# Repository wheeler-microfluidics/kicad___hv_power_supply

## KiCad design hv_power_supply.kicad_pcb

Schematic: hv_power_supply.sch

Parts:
C1: 100uF, 35V; TantalC_SizeE_EIA-7360_Reflow
C2, C3: 100nF; C_0805
C4: 4u7,250V; c_elec_8x10.5
C5: 10uF; TantalC_SizeD_EIA-7343_Reflow
C6: 100nF,250V; C_1812
D1: ES2F; DO-214BA
L1: 100uH; self_cms_we-pd3
P1: CONN_01X09; Pin_Header_Straight_1x09
Q1: IRF644PBF; TO-220_Neutral123_Vertical
R1: 10k; R_0805
R2: 1M5; R_2512
R5: RSENSE; R_2512
U1: MAX1771; SOIC-8_3.9x4.9mm_Pitch1.27mm
U2: MCP41050; SOIC-8_3.9x4.9mm_Pitch1.27mm

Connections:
CS: P1.5, U2.1 (~CS)
DGND: C1.2, C2.2, C3.2, C4.2, C5.2, C6.2, P1.2, P1.7, R1.2, R5.2, U1.6, U1.7, U2.4 (VSS)
HV: C4.1, C6.1, D1.1 (K), P1.1, R2.1
unnamed: C3.1, U1.5
unnamed: D1.2 (A), L1.1, Q1.2
unnamed: Q1.1, U1.1
unnamed: Q1.3, R5.1, U1.8
unnamed: R1.1, U2.6 (PW0), U2.7 (PB0)
unnamed: R2.2, U1.3, U2.5 (PA0)
PWR: C1.1, L1.2, P1.9
SCK: P1.4, U2.2 (SCK)
SHDN: P1.6, U1.4
SI: P1.3, U2.3 (SI)
VCC: C2.1, C5.1, P1.8, U1.2, U2.8 (VDD)

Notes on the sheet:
9-30V
9-16V
Pin header

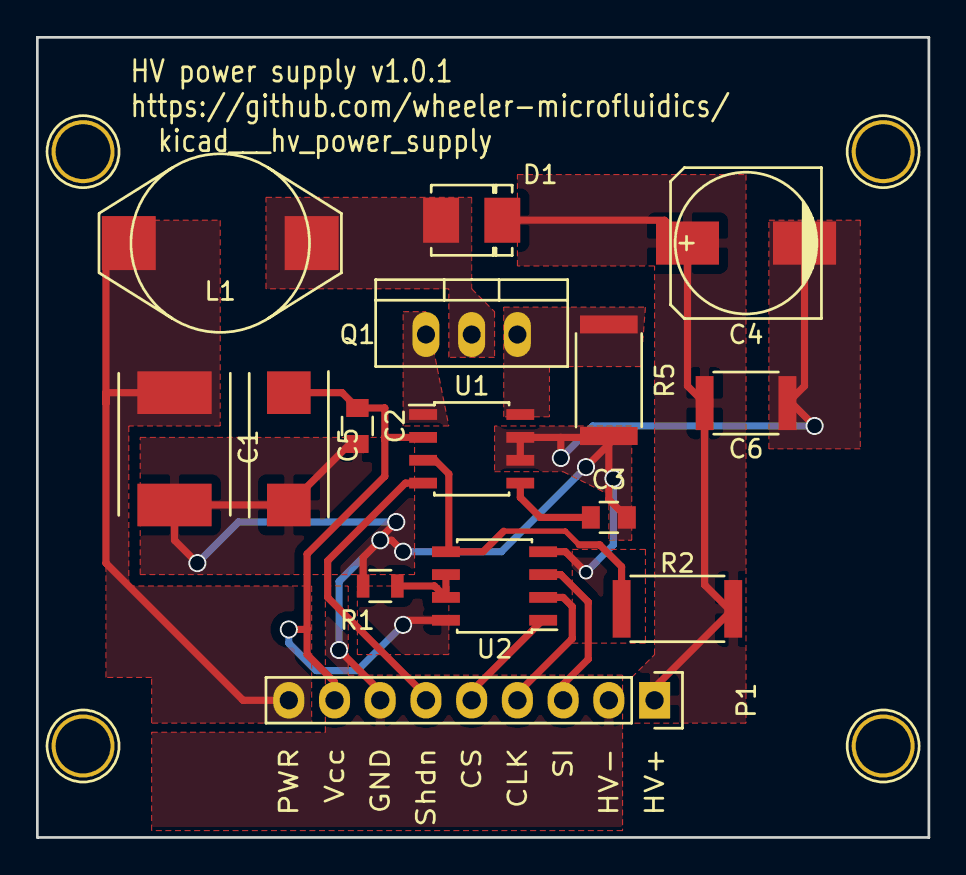
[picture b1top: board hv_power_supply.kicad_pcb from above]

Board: 2 copper layers, 49.5 x 44.5 mm, 15 parts (0 on the bottom side), 14 nets.

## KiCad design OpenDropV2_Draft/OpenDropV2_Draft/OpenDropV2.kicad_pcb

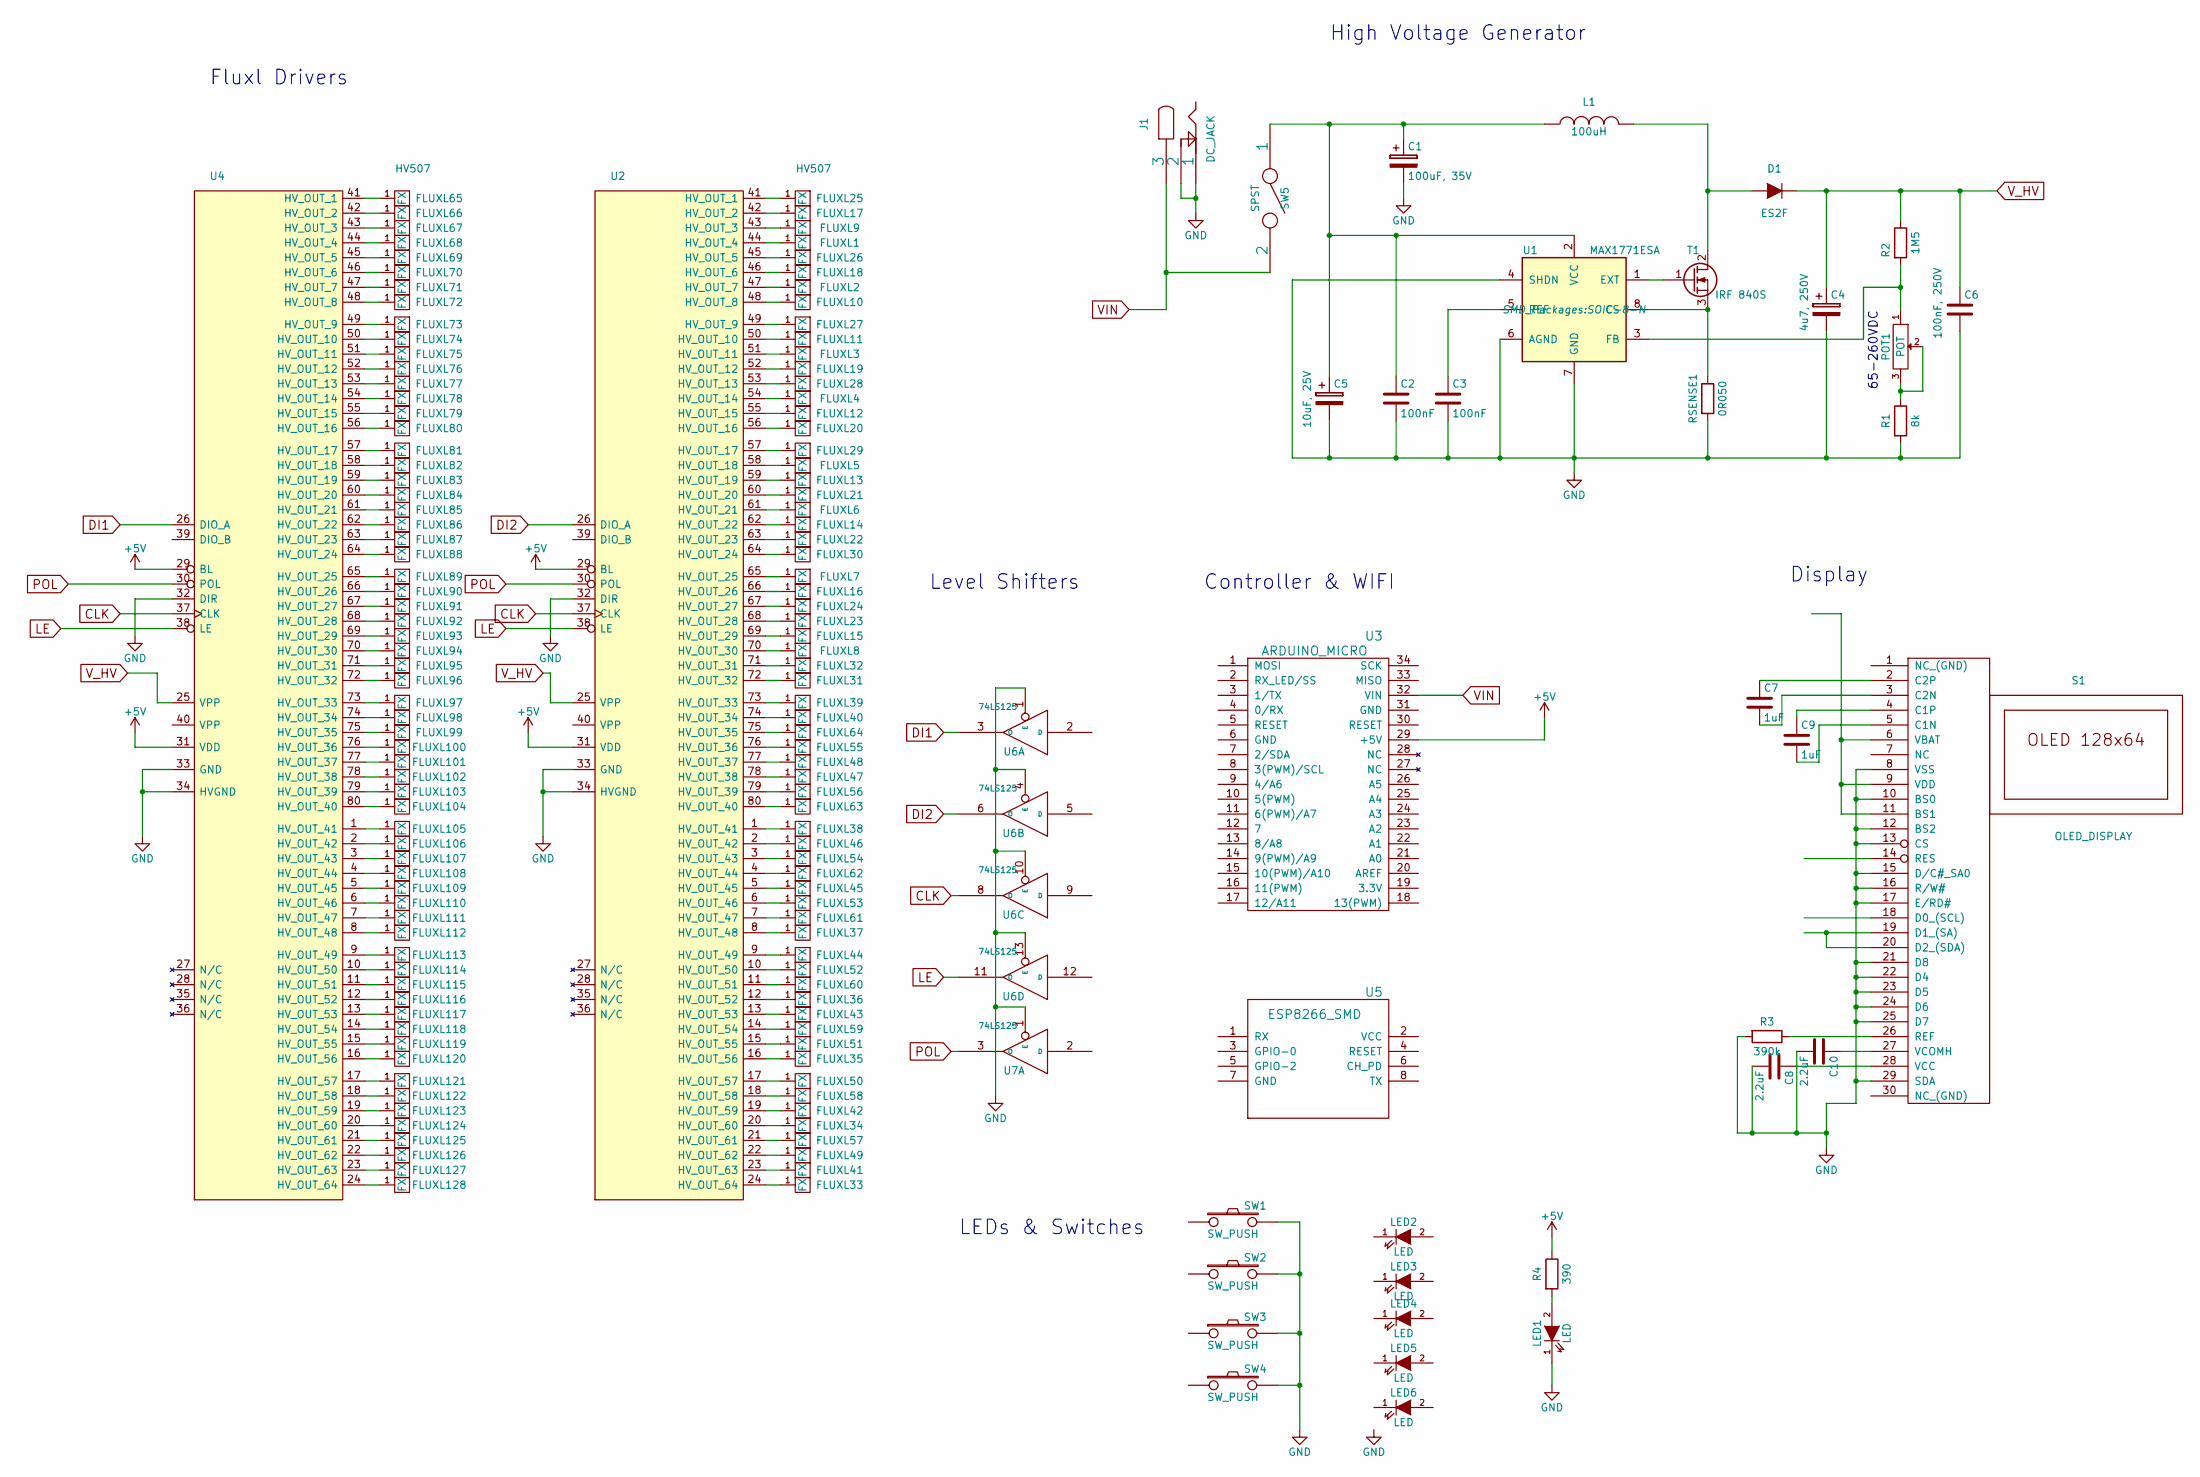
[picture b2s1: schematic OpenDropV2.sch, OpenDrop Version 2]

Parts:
C1: 100uF, 35V; R_2512_HandSoldering
C2, C3: 100nF; C_0805
C4: 4u7, 250V; C_SMD_12mm
C5: 10uF, 25V; C_1210_HandSoldering
C6: 100nF, 250V; R_2512
C7, C9: 1uF; C_0805
C8, C10: 2.2uF; C_0805
D1: ES2F; DO-214AB
FLUXL1, FLUXL2, FLUXL3, FLUXL4, FLUXL5, FLUXL6, FLUXL7, FLUXL8, FLUXL9, FLUXL10, FLUXL11, FLUXL12, FLUXL13, FLUXL14, FLUXL15, FLUXL16, FLUXL17, FLUXL18, FLUXL19, FLUXL20, FLUXL21, FLUXL22, FLUXL23, FLUXL24, FLUXL25, FLUXL26, FLUXL27, FLUXL28, FLUXL29, FLUXL30, FLUXL31, FLUXL32, FLUXL33, FLUXL34, FLUXL35, FLUXL36, FLUXL37, FLUXL38, FLUXL39, FLUXL40, FLUXL41, FLUXL42, FLUXL43, FLUXL44, FLUXL45, FLUXL46, FLUXL47, FLUXL48, FLUXL49, FLUXL50, FLUXL51, FLUXL52, FLUXL53, FLUXL54, FLUXL55, FLUXL56, FLUXL57, FLUXL58, FLUXL59, FLUXL60, FLUXL61, FLUXL62, FLUXL63, FLUXL64, FLUXL65, FLUXL66, FLUXL67, FLUXL68, FLUXL69, FLUXL70, FLUXL71, FLUXL72, FLUXL73, FLUXL74, FLUXL75, FLUXL76, FLUXL77, FLUXL78, FLUXL79, FLUXL80, FLUXL81, FLUXL82, FLUXL83, FLUXL84, FLUXL85, FLUXL86, FLUXL87, FLUXL88, FLUXL89, FLUXL90, FLUXL91, FLUXL92, FLUXL93, FLUXL94, FLUXL95, FLUXL96, FLUXL97, FLUXL98, FLUXL99, FLUXL100, FLUXL101, FLUXL102, FLUXL103, FLUXL104, FLUXL105, FLUXL106, FLUXL107, FLUXL108, FLUXL109, FLUXL110, FLUXL111, FLUXL112, FLUXL113, FLUXL114, FLUXL115, FLUXL116, FLUXL117, FLUXL118, FLUXL119, FLUXL120, FLUXL121, FLUXL122, FLUXL123, FLUXL124, FLUXL125, FLUXL126, FLUXL127, FLUXL128: FX; FLUXL_PAD_2_75
J1: DC_JACK; DC_JACK_SMD
L1: 100uH; Inductor_18.54x15.24
LED1, LED2, LED3, LED4, LED5, LED6: LED; LED_SIDE
POT1: POT; Potentiometer_Trimmer-Suntan-TSR-3386P
R1: 8k; R_0805
R2: 1M5; R_2512
R3: 390k; R_0805
R4: 390; R_0805
RSENSE1: 0R050; R_2010
S1: OLED_DISPLAY; OLED_096_1
SW1, SW2, SW3, SW4: SW_PUSH; SW_SPST_PTS645
SW5: SPST; Switch_On-On
T1: IRF 840S; D2PAK
U1: MAX1771ESA; SOIC-8-N
U2, U4: HV507; PQFP-80_14x20mm_Pitch0.8mm
U3: ARDUINO_MICRO; ARDUINO_MICRO_SMD
U5: ESP8266_SMD
U6, U7: 74LS125; SOIC-14_N

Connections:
+5V: R4.1, U2.29 (BL), U2.31 (VDD), U3.29 (+5V), U4.29 (BL), U4.31 (VDD)
CLK: U2.37 (CLK), U4.37 (CLK), U6.8 (O)
DI1: U4.26 (DIO_A), U6.3 (O)
DI2: U2.26 (DIO_A), U6.6 (O)
GND: C1.2, C2.2, C3.2, C4.2, C5.2, C6.2, C8.2, C10.2, J1.1, J1.2, LED1.1 (K), R1.2, R3.2, RSENSE1.2, S1.8 (VSS), S1.10 (BS0), S1.12 (BS2), S1.13 (CS), S1.15 (D/C#_SA0), S1.16 (R/W#), S1.17 (E/RD#), S1.21 (D8), S1.22 (D4), S1.23 (D5), S1.24 (D6), S1.25 (D7), S1.29 (SDA), SW1.2, SW2.2, SW3.2, SW4.2, U1.4 (SHDN), U1.6 (AGND), U1.7 (GND), U2.32 (DIR), U2.33 (GND), U2.34 (HVGND), U4.32 (DIR), U4.33 (GND), U4.34 (HVGND), U6.1 (E), U6.4 (E), U6.7 (GND), U6.10 (E), U6.13 (E), U7.1 (E)
LE: U2.38 (LE), U4.38 (LE), U6.11 (O)
unnamed: C1.1, C2.1, C5.1, L1.1, SW5.1, U1.2 (VCC)
unnamed: C3.1, U1.5 (REF)
unnamed: C7.1, S1.2 (C2P)
unnamed: C7.2, S1.3 (C2N)
unnamed: C8.1, S1.28 (VCC)
unnamed: C9.1, S1.4 (C1P)
unnamed: C9.2, S1.5 (C1N)
unnamed: C10.1, S1.27 (VCOMH)
unnamed: D1.2 (A), L1.2, T1.2 (D)
unnamed: FLUXL1.1, U2.44 (HV_OUT_4)
unnamed: FLUXL2.1, U2.47 (HV_OUT_7)
unnamed: FLUXL3.1, U2.51 (HV_OUT_11)
unnamed: FLUXL4.1, U2.54 (HV_OUT_14)
unnamed: FLUXL5.1, U2.58 (HV_OUT_18)
unnamed: FLUXL6.1, U2.61 (HV_OUT_21)
unnamed: FLUXL7.1, U2.65 (HV_OUT_25)
unnamed: FLUXL8.1, U2.70 (HV_OUT_30)
unnamed: FLUXL9.1, U2.43 (HV_OUT_3)
unnamed: FLUXL10.1, U2.48 (HV_OUT_8)
unnamed: FLUXL11.1, U2.50 (HV_OUT_10)
unnamed: FLUXL12.1, U2.55 (HV_OUT_15)
unnamed: FLUXL13.1, U2.59 (HV_OUT_19)
unnamed: FLUXL14.1, U2.62 (HV_OUT_22)
unnamed: FLUXL15.1, U2.69 (HV_OUT_29)
unnamed: FLUXL16.1, U2.66 (HV_OUT_26)
unnamed: FLUXL17.1, U2.42 (HV_OUT_2)
unnamed: FLUXL18.1, U2.46 (HV_OUT_6)
unnamed: FLUXL19.1, U2.52 (HV_OUT_12)
unnamed: FLUXL20.1, U2.56 (HV_OUT_16)
unnamed: FLUXL21.1, U2.60 (HV_OUT_20)
unnamed: FLUXL22.1, U2.63 (HV_OUT_23)
unnamed: FLUXL23.1, U2.68 (HV_OUT_28)
unnamed: FLUXL24.1, U2.67 (HV_OUT_27)
unnamed: FLUXL25.1, U2.41 (HV_OUT_1)
unnamed: FLUXL26.1, U2.45 (HV_OUT_5)
unnamed: FLUXL27.1, U2.49 (HV_OUT_9)
unnamed: FLUXL28.1, U2.53 (HV_OUT_13)
unnamed: FLUXL29.1, U2.57 (HV_OUT_17)
unnamed: FLUXL30.1, U2.64 (HV_OUT_24)
unnamed: FLUXL31.1, U2.72 (HV_OUT_32)
unnamed: FLUXL32.1, U2.71 (HV_OUT_31)
unnamed: FLUXL33.1, U2.24 (HV_OUT_64)
unnamed: FLUXL34.1, U2.20 (HV_OUT_60)
unnamed: FLUXL35.1, U2.16 (HV_OUT_56)
unnamed: FLUXL36.1, U2.12 (HV_OUT_52)
unnamed: FLUXL37.1, U2.8 (HV_OUT_48)
unnamed: FLUXL38.1, U2.1 (HV_OUT_41)
unnamed: FLUXL39.1, U2.73 (HV_OUT_33)
unnamed: FLUXL40.1, U2.74 (HV_OUT_34)
unnamed: FLUXL41.1, U2.23 (HV_OUT_63)
unnamed: FLUXL42.1, U2.19 (HV_OUT_59)
unnamed: FLUXL43.1, U2.13 (HV_OUT_53)
unnamed: FLUXL44.1, U2.9 (HV_OUT_49)
unnamed: FLUXL45.1, U2.5 (HV_OUT_45)
unnamed: FLUXL46.1, U2.2 (HV_OUT_42)
unnamed: FLUXL47.1, U2.78 (HV_OUT_38)
unnamed: FLUXL48.1, U2.77 (HV_OUT_37)
unnamed: FLUXL49.1, U2.22 (HV_OUT_62)
unnamed: FLUXL50.1, U2.17 (HV_OUT_57)
unnamed: FLUXL51.1, U2.15 (HV_OUT_55)
unnamed: FLUXL52.1, U2.10 (HV_OUT_50)
unnamed: FLUXL53.1, U2.6 (HV_OUT_46)
unnamed: FLUXL54.1, U2.3 (HV_OUT_43)
unnamed: FLUXL55.1, U2.76 (HV_OUT_36)
unnamed: FLUXL56.1, U2.79 (HV_OUT_39)
unnamed: FLUXL57.1, U2.21 (HV_OUT_61)
unnamed: FLUXL58.1, U2.18 (HV_OUT_58)
unnamed: FLUXL59.1, U2.14 (HV_OUT_54)
unnamed: FLUXL60.1, U2.11 (HV_OUT_51)
unnamed: FLUXL61.1, U2.7 (HV_OUT_47)
unnamed: FLUXL62.1, U2.4 (HV_OUT_44)
unnamed: FLUXL63.1, U2.80 (HV_OUT_40)
unnamed: FLUXL64.1, U2.75 (HV_OUT_35)
unnamed: FLUXL65.1, U4.41 (HV_OUT_1)
unnamed: FLUXL66.1, U4.42 (HV_OUT_2)
unnamed: FLUXL67.1, U4.43 (HV_OUT_3)
unnamed: FLUXL68.1, U4.44 (HV_OUT_4)
unnamed: FLUXL69.1, U4.45 (HV_OUT_5)
unnamed: FLUXL70.1, U4.46 (HV_OUT_6)
unnamed: FLUXL71.1, U4.47 (HV_OUT_7)
unnamed: FLUXL72.1, U4.48 (HV_OUT_8)
unnamed: FLUXL73.1, U4.49 (HV_OUT_9)
unnamed: FLUXL74.1, U4.50 (HV_OUT_10)
unnamed: FLUXL75.1, U4.51 (HV_OUT_11)
unnamed: FLUXL76.1, U4.52 (HV_OUT_12)
unnamed: FLUXL77.1, U4.53 (HV_OUT_13)
unnamed: FLUXL78.1, U4.54 (HV_OUT_14)
unnamed: FLUXL79.1, U4.55 (HV_OUT_15)
unnamed: FLUXL80.1, U4.56 (HV_OUT_16)
unnamed: FLUXL81.1, U4.57 (HV_OUT_17)
unnamed: FLUXL82.1, U4.58 (HV_OUT_18)
unnamed: FLUXL83.1, U4.59 (HV_OUT_19)
unnamed: FLUXL84.1, U4.60 (HV_OUT_20)
unnamed: FLUXL85.1, U4.61 (HV_OUT_21)
unnamed: FLUXL86.1, U4.62 (HV_OUT_22)
unnamed: FLUXL87.1, U4.63 (HV_OUT_23)
unnamed: FLUXL88.1, U4.64 (HV_OUT_24)
unnamed: FLUXL89.1, U4.65 (HV_OUT_25)
unnamed: FLUXL90.1, U4.66 (HV_OUT_26)
unnamed: FLUXL91.1, U4.67 (HV_OUT_27)
unnamed: FLUXL92.1, U4.68 (HV_OUT_28)
unnamed: FLUXL93.1, U4.69 (HV_OUT_29)
unnamed: FLUXL94.1, U4.70 (HV_OUT_30)
unnamed: FLUXL95.1, U4.71 (HV_OUT_31)
unnamed: FLUXL96.1, U4.72 (HV_OUT_32)
unnamed: FLUXL97.1, U4.73 (HV_OUT_33)
unnamed: FLUXL98.1, U4.74 (HV_OUT_34)
unnamed: FLUXL99.1, U4.75 (HV_OUT_35)
unnamed: FLUXL100.1, U4.76 (HV_OUT_36)
unnamed: FLUXL101.1, U4.77 (HV_OUT_37)
unnamed: FLUXL102.1, U4.78 (HV_OUT_38)
unnamed: FLUXL103.1, U4.79 (HV_OUT_39)
unnamed: FLUXL104.1, U4.80 (HV_OUT_40)
unnamed: FLUXL105.1, U4.1 (HV_OUT_41)
unnamed: FLUXL106.1, U4.2 (HV_OUT_42)
unnamed: FLUXL107.1, U4.3 (HV_OUT_43)
unnamed: FLUXL108.1, U4.4 (HV_OUT_44)
unnamed: FLUXL109.1, U4.5 (HV_OUT_45)
unnamed: FLUXL110.1, U4.6 (HV_OUT_46)
unnamed: FLUXL111.1, U4.7 (HV_OUT_47)
unnamed: FLUXL112.1, U4.8 (HV_OUT_48)
unnamed: FLUXL113.1, U4.9 (HV_OUT_49)
unnamed: FLUXL114.1, U4.10 (HV_OUT_50)
unnamed: FLUXL115.1, U4.11 (HV_OUT_51)
unnamed: FLUXL116.1, U4.12 (HV_OUT_52)
unnamed: FLUXL117.1, U4.13 (HV_OUT_53)
unnamed: FLUXL118.1, U4.14 (HV_OUT_54)
unnamed: FLUXL119.1, U4.15 (HV_OUT_55)
unnamed: FLUXL120.1, U4.16 (HV_OUT_56)
unnamed: FLUXL121.1, U4.17 (HV_OUT_57)
unnamed: FLUXL122.1, U4.18 (HV_OUT_58)
unnamed: FLUXL123.1, U4.19 (HV_OUT_59)
unnamed: FLUXL124.1, U4.20 (HV_OUT_60)
unnamed: FLUXL125.1, U4.21 (HV_OUT_61)
unnamed: FLUXL126.1, U4.22 (HV_OUT_62)
unnamed: FLUXL127.1, U4.23 (HV_OUT_63)
unnamed: FLUXL128.1, U4.24 (HV_OUT_64)
unnamed: LED1.2 (A), R4.2
unnamed: POT1.1, R2.2, U1.3 (FB)
unnamed: POT1.2, POT1.3, R1.1
unnamed: R3.1, S1.26 (REF)
unnamed: RSENSE1.1, T1.3 (S), U1.8 (CS)
unnamed: S1.6 (VBAT), S1.9 (VDD), S1.11 (BS1)
unnamed: S1.19 (D1_(SA)), S1.20 (D2_(SDA))
unnamed: T1.1 (G), U1.1 (EXT)
POL: U2.30 (POL), U4.30 (POL), U7.3 (O)
VIN: J1.3, SW5.2, U3.32 (VIN)
V_HV: C4.1, C6.1, D1.1 (K), R2.1, U2.25 (VPP), U4.25 (VPP)

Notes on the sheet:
65-260VDC
High Voltage Generator
Fluxl Drivers
Controller & WIFI
Display
Level Shifters
LEDs & Switches

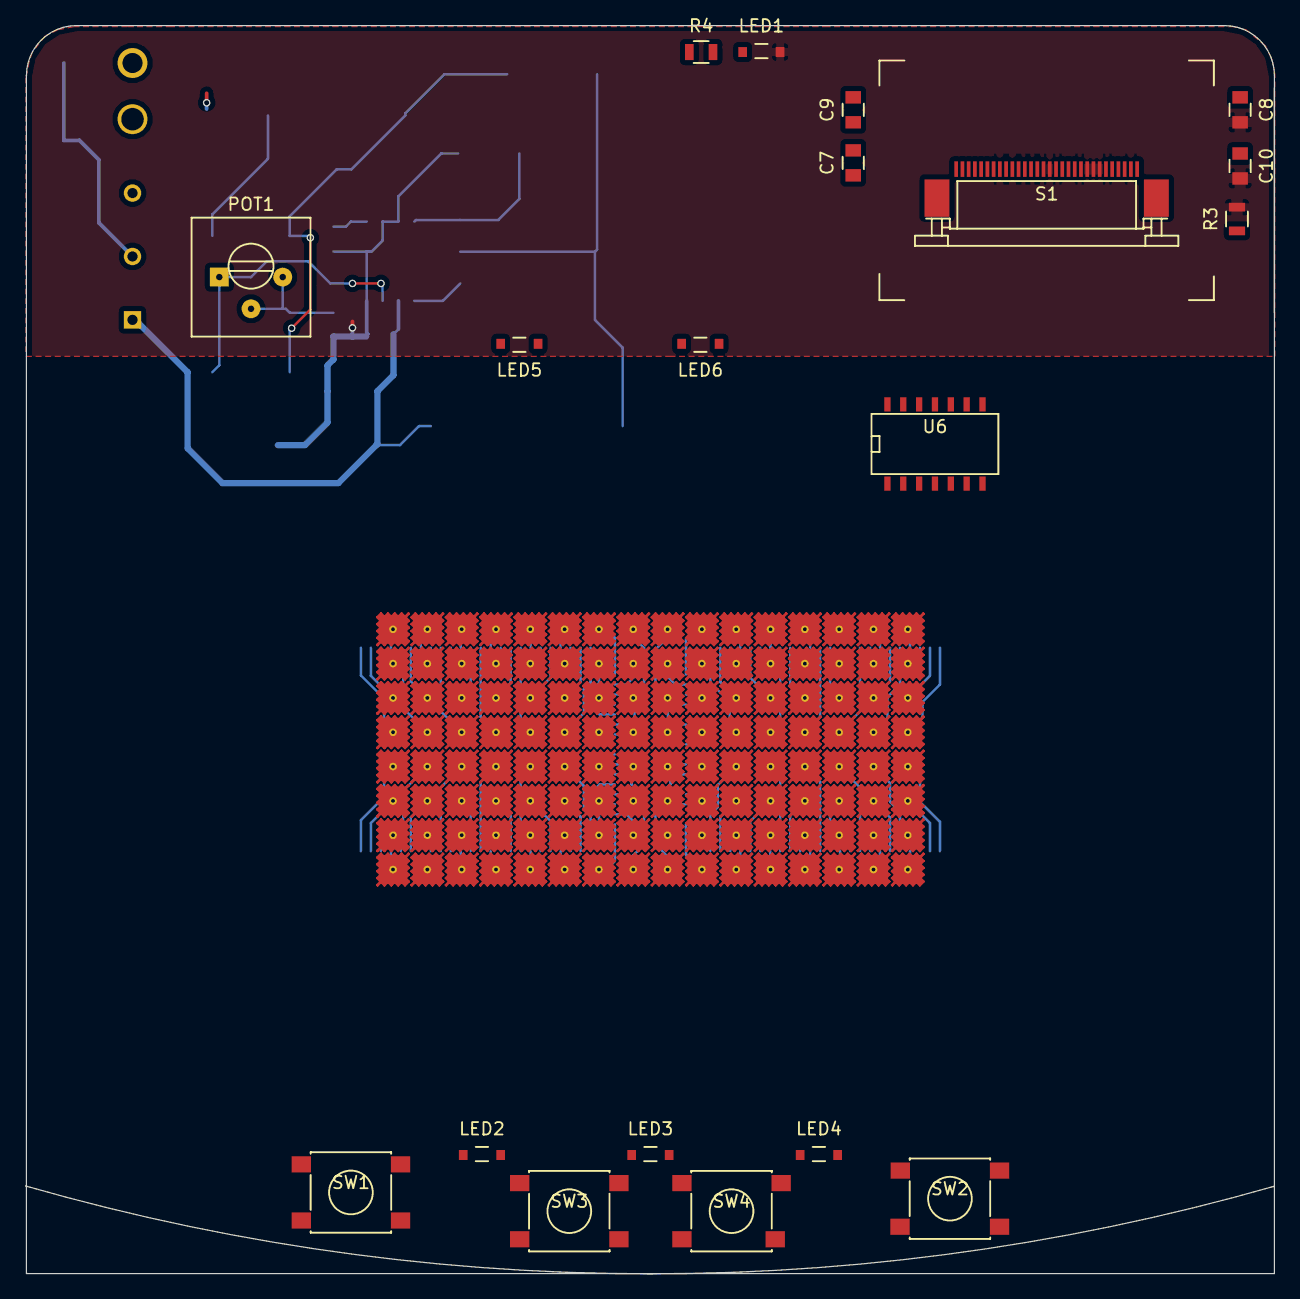
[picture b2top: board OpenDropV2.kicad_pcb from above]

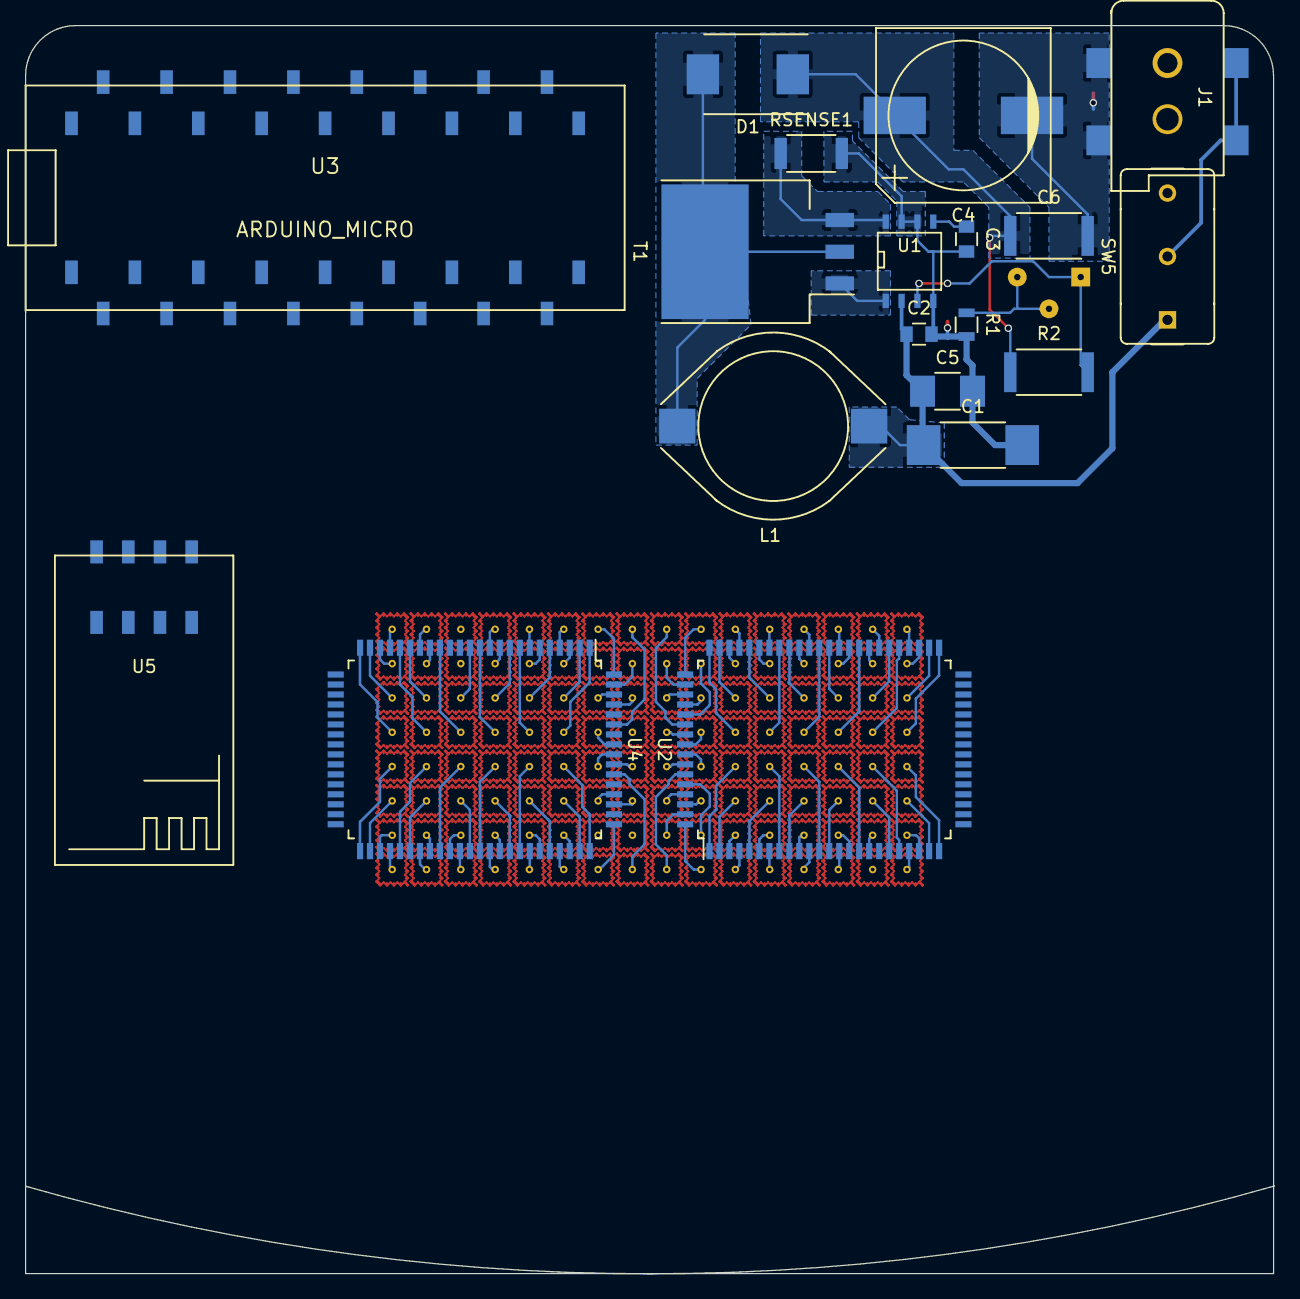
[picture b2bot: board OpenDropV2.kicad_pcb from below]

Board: 2 copper layers, 100.1 x 100.0 mm, 166 parts (19 on the bottom side), 154 nets.

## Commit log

2015-10-19 :lollipop: Added .gitattributes & .gitignore files
2015-10-19 Nixie High Voltage PSU with Digital Pot
    Schematic, Library files, PCD layout
2016-01-28 Remove unnecessary files and copy parts to wheelerlab library
2016-01-28 Rename to hv_power_supply
2016-01-28 Add holes and labels
2016-01-28 Break out all pins on 9x1 header
2016-01-28 Add gerber files
2016-01-29 Mover gerbers to subdirectory
2016-02-11 Add extra via holes to connect back side of single-sided board
2017-07-13 added appveyor.yml
2017-07-14 AppVeyor Configuration Updated
2017-07-18 AppVeyor Update: "a4e909ac7a44d2708564d46a9b978b95c8367686"
2017-07-19 AppVeyor Update: "d5d159050eac48ab9123f383fe8e949476d7f60f"
2017-07-20 AppVeyor Update: "35852f667457a927c170bb71278740b12d7a8f75"
